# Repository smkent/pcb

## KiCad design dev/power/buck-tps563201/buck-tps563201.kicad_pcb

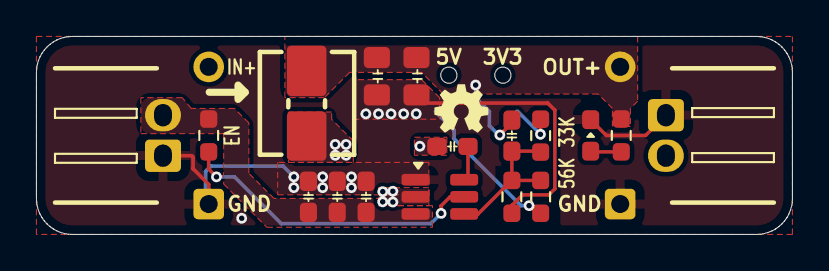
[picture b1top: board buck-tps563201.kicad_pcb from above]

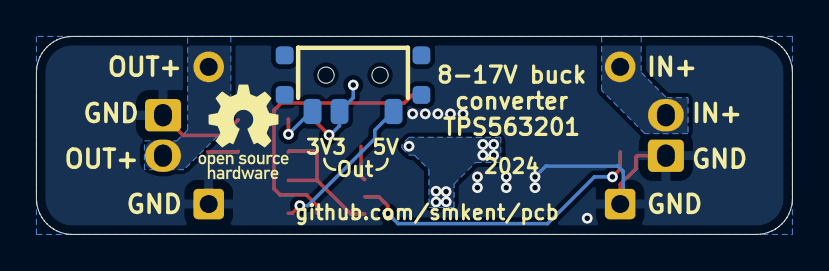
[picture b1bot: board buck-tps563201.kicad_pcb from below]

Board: 2 copper layers, 42.0 x 11.0 mm, 22 parts (5 on the bottom side), 10 nets.

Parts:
C1, C2: 10u; C_0603_1608Metric_Pad1.08x0.95mm_HandSolder
C3, C7: 0u1; C_0603_1608Metric_Pad1.08x0.95mm_HandSolder
C4: 75p; C_0603_1608Metric_Pad1.08x0.95mm_HandSolder
C8, C9: 22u; C_0805_2012Metric_Pad1.18x1.45mm_HandSolder
J1, J4: Conn_01x02; Conn_Combo_JST-1x02-XH_PH-THT-pad2gnd
J2, J5: Conn_01x03; PinHeader_1x01_P2.54mm_simple
J3, J6: Conn_01x03; PinHeader_1x01_P2.54mm_simple_square
L1: 4u7; Inductor_Multi_5.2x5.7_2x2.5
LED1: LED_Small; LED_0603_1608Metric_Pad1.05x0.95mm_HandSolder_simple
R0, R1, R4: 10K; R_0603_1608Metric_Pad0.98x0.95mm_HandSolder
R2: 56K; R_0603_1608Metric_Pad0.98x0.95mm_HandSolder
R3: 33K; R_0603_1608Metric_Pad0.98x0.95mm_HandSolder
SW1: SW_SPDT; SW-SMD_3P-P1.50_L2.7-W6.6
U1: TPS563200; SOT-23-6_Handsoldering_simple

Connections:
FB: C4.1, R1.2, R2.1, R3.2, U1.4 (VFB)
GND: C1.2, C2.2, C3.2, C8.2, C9.2, J1.2, J3.1, J4.2, J6.1, LED1.1 (K), R1.1, U1.1 (GND)
unnamed: LED1.2 (A), R0.1
unnamed: R2.2, SW1.1 (A)
unnamed: R3.1, SW1.3 (C)
unnamed: R4.2, U1.5 (EN)
unnamed: C7.1, U1.6 (VBST)
SW: C7.2, L1.1, U1.2 (SW)
VIN: C1.1, C2.1, C3.1, J1.1, J2.1, R4.1, U1.3 (VIN)
VOUT: C4.2, C8.1, C9.1, J4.1, J5.1, L1.2, R0.2, SW1.2 (B)

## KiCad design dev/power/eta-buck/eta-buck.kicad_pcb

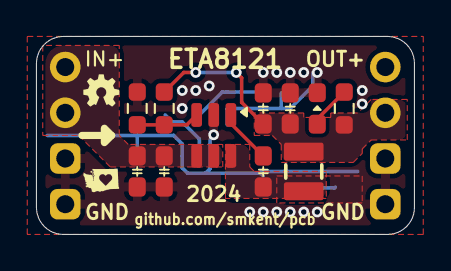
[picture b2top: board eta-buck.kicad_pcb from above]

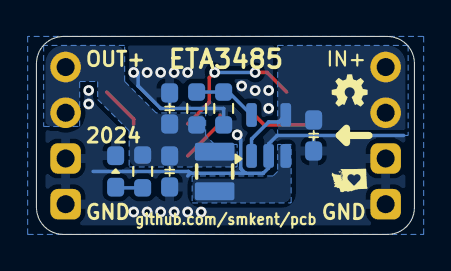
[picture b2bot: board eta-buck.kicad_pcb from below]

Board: 2 copper layers, 21.0 x 11.0 mm, 22 parts (11 on the bottom side), 10 nets.

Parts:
C0, C1, C4: 10u; C_0603_1608Metric_Pad1.08x0.95mm_HandSolder
C2, C3, C5, C6: 22u; C_0603_1608Metric_Pad1.08x0.95mm_HandSolder
C7: 10n; C_0603_1608Metric_Pad1.08x0.95mm_HandSolder
J1, J2: Pin headers; PinHeader_1x04_P2.54mm_Vertical_simple_pad3,4gnd
L1, L2: 4u7; IND-SMD_L2.5-W2.0_MHCHL2520
LED1, LED2: LED_Small; LED_0603_1608Metric_Pad1.05x0.95mm_HandSolder_simple
R1: 56K; R_0603_1608Metric_Pad0.98x0.95mm_HandSolder
R2, R3, R5, R6: 10K; R_0603_1608Metric_Pad0.98x0.95mm_HandSolder
R4: 75K; R_0603_1608Metric_Pad0.98x0.95mm_HandSolder
U1: ETA8121; SOT-23-6_simple
U2: ETA3485; SOT-23-5_simple

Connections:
/SW_B: L2.1, U2.3 (SW)
/SW_F: C7.2, L1.1, U1.6 (SW)
FB_B: R4.1, R5.2, U2.5 (FB)
FB_F: R1.1, R2.2, U1.3 (FB)
GND: C0.2, C1.2, C2.2, C3.2, C4.2, C5.2, C6.2, J1.3, J1.4, J2.3, J2.4, LED1.1 (K), LED2.1 (K), R2.1, R5.1, U1.2 (GND), U2.2 (GND)
unnamed: LED1.2 (A), R3.1
unnamed: LED2.2 (A), R6.1
unnamed: C7.1, U1.1 (BST)
VIN: C0.1, C1.1, C4.1, J1.1, J1.2, U1.4 (EN), U1.5 (VIN), U2.1 (EN), U2.4 (IN)
VOUT: C2.1, C3.1, C5.1, C6.1, J2.1, J2.2, L1.2, L2.2, R1.2, R3.2, R4.2, R6.2

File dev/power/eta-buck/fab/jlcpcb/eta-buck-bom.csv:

Comment,Designator,Footprint,LCSC
LED_Small,"LED1,LED2",custom:LED_0603_1608Metric_Pad1.05x0.95mm_HandSolder_simple,
10n,C7,custom:C_0603_1608Metric_Pad1.08x0.95mm_HandSolder,
56K,R1,Resistor_SMD:R_0603_1608Metric_Pad0.98x0.95mm_HandSolder,
ETA8121,U1,custom:SOT-23-6_simple,C7465509
75K,R4,Resistor_SMD:R_0603_1608Metric_Pad0.98x0.95mm_HandSolder,
10K,"R2,R3,R5,R6",Resistor_SMD:R_0603_1608Metric_Pad0.98x0.95mm_HandSolder,
22u,"C2,C3,C5,C6",custom:C_0603_1608Metric_Pad1.08x0.95mm_HandSolder,
10u,"C0,C1,C4",custom:C_0603_1608Metric_Pad1.08x0.95mm_HandSolder,
ETA3485,U2,custom:SOT-23-5_simple,C7465518
Pin headers,"J1,J2","custom:PinHeader_1x04_P2.54mm_Vertical_simple_pad3,4gnd",
4u7,"L1,L2",lcsc:IND-SMD_L2.5-W2.0_MHCHL2520,

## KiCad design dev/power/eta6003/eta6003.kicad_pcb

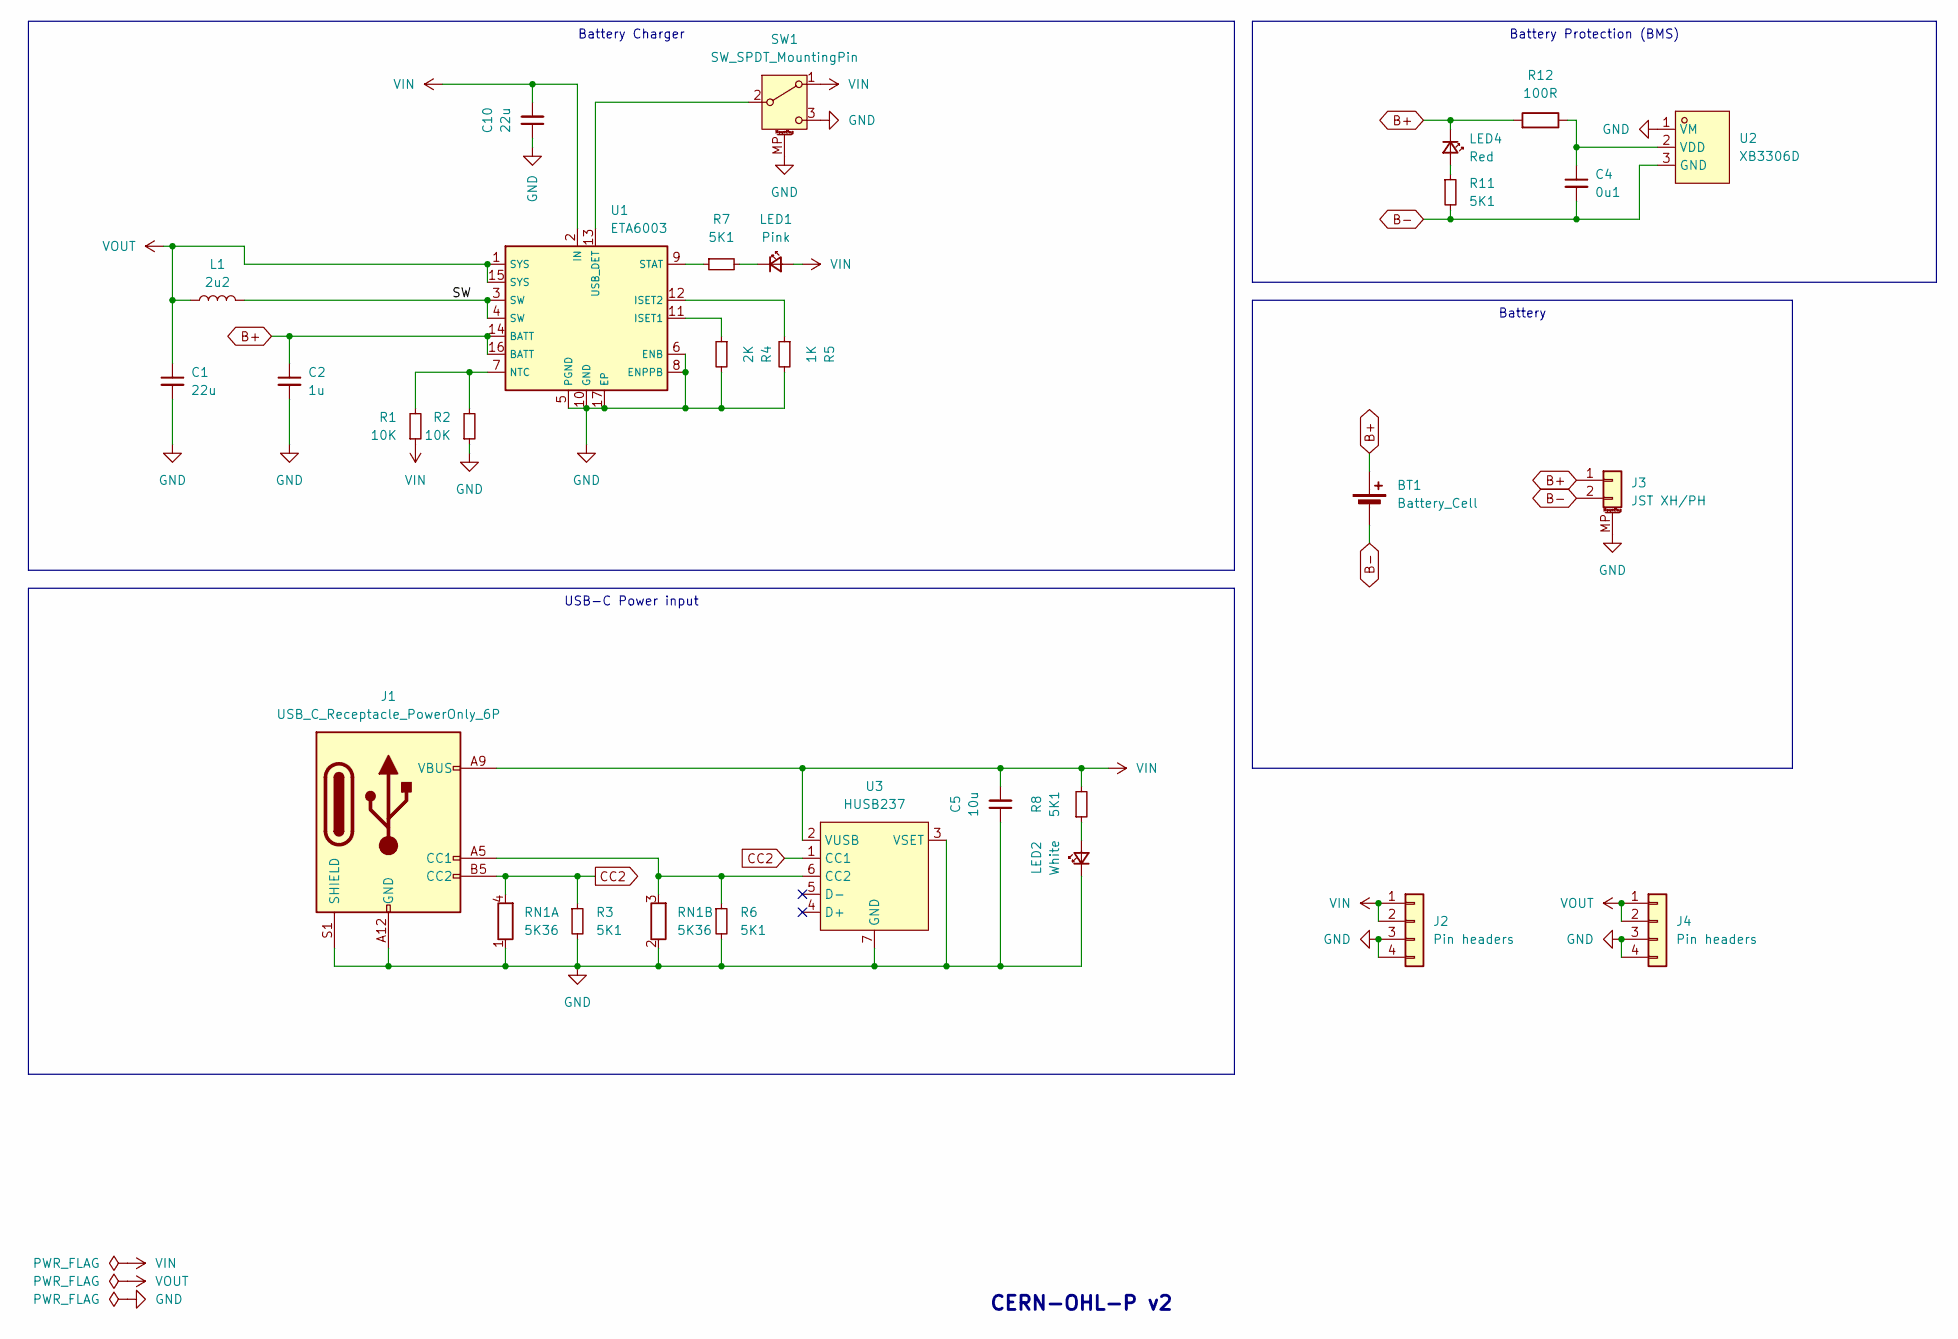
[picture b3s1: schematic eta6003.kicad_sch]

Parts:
BT1: Battery_Cell; BAT-TH_18650-A5BJ001
C1: 22u; C_0603_1608Metric_Pad1.08x0.95mm_HandSolder; LCSC Part C45783
C2: 1u; C_0603_1608Metric_Pad1.08x0.95mm_HandSolder; LCSC Part C52923
C4: 0u1; C_0603_1608Metric_Pad1.08x0.95mm_HandSolder; LCSC Part C1525
C5: 10u; C_0603_1608Metric_Pad1.08x0.95mm_HandSolder; LCSC Part C15850
C10: 22u; C_0805_2012Metric_Pad1.18x1.45mm_wide-center_HandSolder; LCSC Part C15850
J1: USB_C_Receptacle_PowerOnly_6P; USB_C_Receptacle_GCT_USB4125-xx-x_6P_TopMnt_Horizontal_hand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; LCSC Part C2927029
J2, J4: Pin headers; PinHeader_1x04_P2.54mm_Vertical_simple_pad3,4gnd
J3: JST XH/PH; Conn_Combo_JST-1x02-XH_PH-SMD-alt-pad2gnd
L1: 2u2; IND-SMD_L2.5-W2.0_MHCHL2520; LCSC Part C5832372
LED1: Pink; LED_0603_1608Metric_Pad1.05x0.95mm_HandSolder_simple
LED2: White; LED_0603_1608Metric_Pad1.05x0.95mm_HandSolder_simple
LED4: Red; LED_0603_1608Metric_Pad1.05x0.95mm_HandSolder_simple; LCSC Part C2286
R1, R2: 10K; R_0603_1608Metric_Pad0.98x0.95mm_HandSolder_simple; LCSC Part C25744
R3, R6, R11: 5K1; R_0603_1608Metric_Pad0.98x0.95mm_HandSolder_simple; LCSC Part C25905
R4: 2K; R_0603_1608Metric_Pad0.98x0.95mm_HandSolder; LCSC Part C22975
R5: 1K; R_0603_1608Metric_Pad0.98x0.95mm_HandSolder; LCSC Part C21190
R7, R8: 5K1; R_0603_1608Metric_Pad0.98x0.95mm_HandSolder_simple; LCSC Part C21190
R12: 100R; R_0603_1608Metric_Pad0.98x0.95mm_HandSolder_simple; LCSC Part C25076
RN1: 5K36; R_Array_Convex_2x0402
SW1: SW_SPDT_MountingPin; SW-SMD_3P-P1.50_L2.7-W6.6
U1: ETA6003; ETA6003_QFN-16-1EP_3x3mm_P0.5mm_EP1.7x1.7mm_ThermalVias; LCSC Part C5455585
U2: XB3306D; SOT-23_simple; LCSC Part C2759992
U3: HUSB237; DFN-6-1EP_2x2mm_P0.65mm_EP1x1.6mm; LCSC Part C7471904

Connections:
/SW: L1.2, U1.3 (SW), U1.4 (SW)
B+: BT1.1 (+), C2.1, J3.1, LED4.1 (K), R12.2, U1.14 (BATT), U1.16 (BATT)
B-: BT1.2 (-), C4.2, J3.2, R11.2, U2.3 (GND)
CC2: J1.B5 (CC2), R3.1, RN1.4 (R1.2), U3.1 (CC1)
GND: C1.2, C2.2, C5.1, C10.1, J1.A12 (GND), J1.B12 (GND), J1.S1 (SHIELD), J2.3, J2.4, J3.MP (MountPin), J4.3, J4.4, LED2.1 (K), R2.1, R3.2, R4.2, R5.2, R6.2, RN1.1 (R1.1), RN1.2 (R2.1), SW1.3 (C), SW1.MP (MountPin), U1.5 (PGND), U1.6 (ENB), U1.8 (ENPPB), U1.10 (GND), U1.17 (EP), U2.1 (VM), U3.3 (VSET), U3.7 (GND)
unnamed: J1.A5 (CC1), R6.1, RN1.3 (R2.2), U3.6 (CC2)
unnamed: LED1.1 (K), R7.2
unnamed: LED2.2 (A), R8.1
unnamed: LED4.2 (A), R11.1
unnamed: SW1.2 (B), U1.13 (USB_DET)
unnamed: R4.1, U1.11 (ISET1)
unnamed: R5.1, U1.12 (ISET2)
unnamed: R1.2, R2.2, U1.7 (NTC)
unnamed: R7.1, U1.9 (STAT)
unnamed: C4.1, R12.1, U2.2 (VDD)
VIN: C5.2, C10.2, J1.A9 (VBUS), J1.B9 (VBUS), J2.1, J2.2, LED1.2 (A), R1.1, R8.2, SW1.1 (A), U1.2 (IN), U3.2 (VUSB)
VOUT: C1.1, J4.1, J4.2, L1.1, U1.1 (SYS), U1.15 (SYS)

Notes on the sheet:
USB-C Power input
Battery Protection (BMS)
Battery Charger
Battery
CERN-OHL-P v2

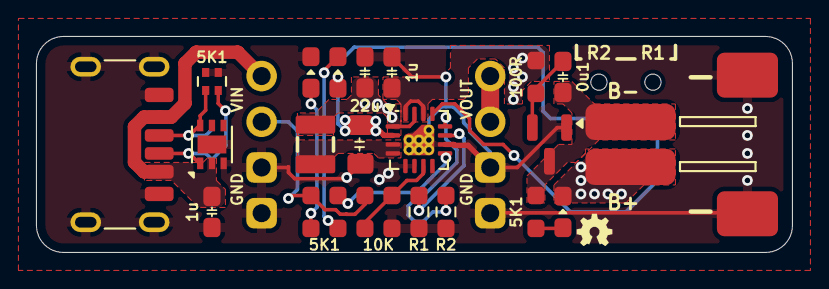
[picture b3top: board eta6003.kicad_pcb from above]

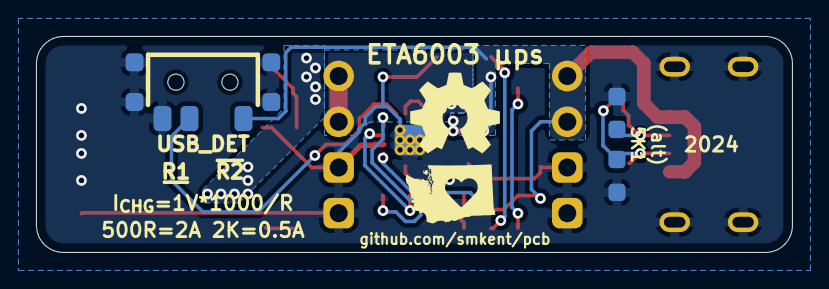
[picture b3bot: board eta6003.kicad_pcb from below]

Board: 2 copper layers, 42.0 x 12.0 mm, 28 parts (5 on the bottom side), 17 nets.

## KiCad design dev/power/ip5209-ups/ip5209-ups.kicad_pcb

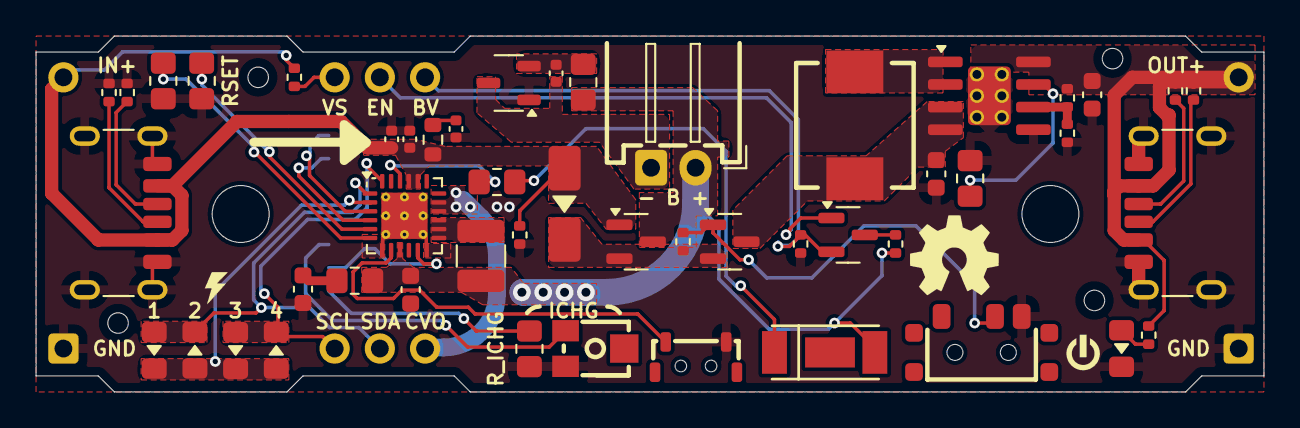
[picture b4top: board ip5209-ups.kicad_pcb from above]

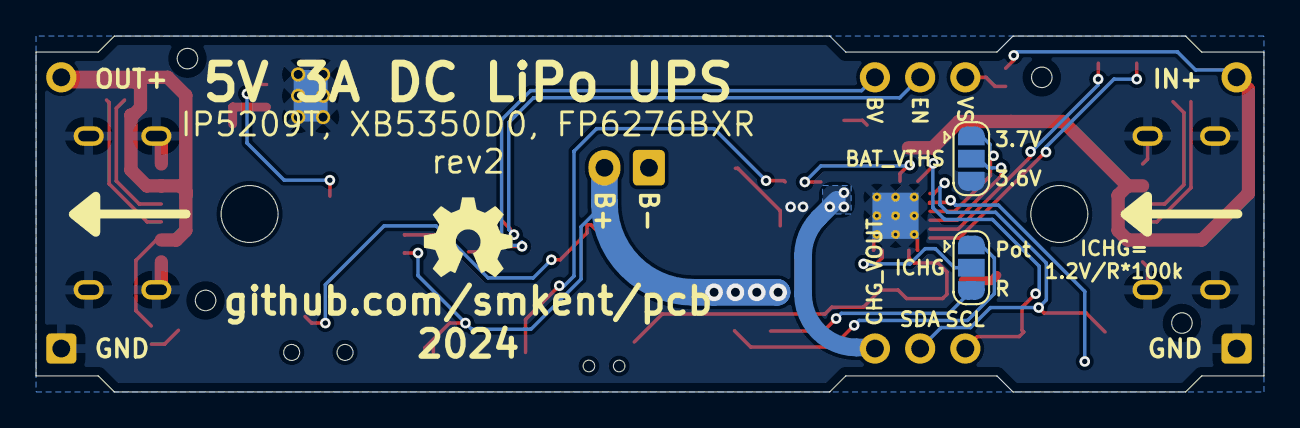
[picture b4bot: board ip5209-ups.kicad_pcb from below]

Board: 2 copper layers, 69.0 x 20.0 mm, 57 parts (8 on the bottom side), 38 nets.

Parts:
BT1: Battery_Cell; JST_XH_S2B-XH-2AW_1x02_P2.50mm_pad2gnd_trim
C1, C6: 10uF; C_0402_1005Metric
C2, C7, C10, C11: 22uF; C_0603_1608Metric
C3: 100nF; C_0402_1005Metric
C9: 0.1uF; C_0402_1005Metric
D1: SS34; D_SMA_simple
J1, J2: USB_C_Receptacle_PowerOnly_6P; USB_C_Receptacle_GCT_USB4125-xx-x_6P_TopMnt_Horizontal_hand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
J3, J9: Conn_01x03; PinHeader_1x03_P2.54mm_Vertical_simple
J5, J8: Conn_01x01; PinHeader_1x01_P2.54mm_simple
J11, J12: Conn_01x01; PinHeader_1x01_P2.54mm_simple_square
JP1, JP2: SolderJumper_3_Open; SolderJumper-3_P1.3mm_Open_RoundedPad1.0x1.5mm
L1: 1uH; L_1210_3225Metric
L2: 4.7uH; IND-SMD_L7.0-W6.6
LED1, LED2, LED3, LED4: LED_0805_2012Metric_Pad1.15x1.40mm_HandSolder_simple
LED5: LED-SMD_3P-L5.7-W3.0-RD
LED6: Boost; LED_0805_2012Metric_Pad1.15x1.40mm_HandSolder_simple
Q1, Q2: AO3401A; SOT-23
Q3: BSS138; SOT-23
R1: 120K; R_0805_2012Metric_Pad1.20x1.40mm_HandSolder
R2: 20R; R_0805_2012Metric_Pad1.20x1.40mm_HandSolder
R3: 2R; R_0603_1608Metric
R4: 0R5; R_0805_2012Metric_Pad1.20x1.40mm_HandSolder
R5: 100R; R_0805_2012Metric_Pad1.20x1.40mm_HandSolder
R6, R7, R9, R10, R13, R14, R15, R16, R17: 10K; R_0402_1005Metric
R8: 75K; R_0402_1005Metric
R11, R12: 5K1; R_0402_1005Metric
R18: 10K; R_0805_2012Metric_Pad1.20x1.40mm_HandSolder
R19: 47K; R_0805_2012Metric_Pad1.20x1.40mm_HandSolder
R20: 0R; R_0805_2012Metric_Pad1.20x1.40mm_HandSolder
RV1: R_Potentiometer_US; RES-ADJ-SMD_VG039NCH
SW1: SW_Push; SW-SMD_BZCN_TSA002A35XXX
SW2: SW_SPDT; SW-SMD_3P-P1.50_L2.7-W6.6
U1: IP5209T; QFN-24-1EP_4x4mm_P0.5mm_EP2.6x2.6mm_ThermalVias
U2: XB3306D; SOT-23-3
U3: FP6276BXR-G1; SOIC-8-1EP_3.9x4.9mm_P1.27mm_EP2.41x3.3mm_ThermalVias_Custo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

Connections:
B+: BT1.1 (+), C2.1, L1.2, LED5.2 (A), Q1.3 (D), R4.1, R5.1, R15.1, U1.9 (BAT)
B-: BT1.2 (-), C9.1, U2.3 (GND)
BATVDD: C9.2, R5.2, U2.2 (VDD)
BAT_SENSE: J9.1, Q3.2 (S), R16.1
BAT_SENSE_ENABLE: J9.2, Q3.1 (G)
BOOST: C10.1, L2.1, Q2.3 (D), U3.3 (VIN), U3.4 (EN)
BOOST_OC: R19.2, U3.7 (OC)
BOOST_SW: L2.2, U3.1 (LX), U3.2 (LX)
CHARGE_VOUT: J3.3, U1.16 (VOUT), U1.17 (VOUT)
FB: R8.2, R9.1, U3.6 (FB)
GND: C1.2, C2.2, C3.2, C6.2, C7.2, C10.2, C11.2, J1.A12 (GND), J1.B12 (GND), J1.S1 (SHIELD), J2.A12 (GND), J2.B12 (GND), J2.S1 (SHIELD), J11.1, J12.1, JP1.3 (B), LED6.1 (K), R1.2, R6.2, R9.2, R11.2, R12.2, R16.2, R18.2, R19.1, R20.1, RV1.3, SW1.1, SW2.3 (C), U1.7 (AGND), U1.12 (PGND), U1.25 (EP), U2.1 (VM), U3.5 (GND), U3.9 (EP)
ICHG: JP2.2 (C), U1.11 (ICHG)
KEY: SW1.2, U1.8 (KEY)
LED1: J3.1, LED3.2 (A), LED4.1 (K), U1.24 (L1)
LED2: J3.2, LED1.2 (A), LED2.1 (K), U1.1 (L2)
LED3: LED1.1 (K), LED2.2 (A), LED3.1 (K), LED4.2 (A), U1.2 (L3)
LIGHT: R2.1, U1.22 (LIGHT)
LOAD_SWITCH: D1.1 (K), Q1.2 (S), Q2.2 (S), R7.1
unnamed: C6.1, R3.2
unnamed: C7.1, R4.2
unnamed: J1.A5 (CC1), R12.1
unnamed: J1.B5 (CC2), R11.1
unnamed: J2.A5 (CC1), R13.2
unnamed: J2.B5 (CC2), R14.2
unnamed: JP2.1 (A), RV1.1
unnamed: JP2.3 (B), R1.1
unnamed: LED5.1 (K), R2.2
unnamed: LED6.2 (A), R10.2
unnamed: Q2.1 (G), R7.2, SW2.2 (B)
unnamed: Q3.3 (D), R15.2
unnamed: R20.2, U1.6 (NTC)
POWER_IN_SENSE: J9.3, R17.2
RSET: R18.1, U1.5 (RSET)
SW: L1.1, U1.13 (LX), U1.14 (LX), U1.15 (LX)
VIN: C1.1, C3.1, D1.2 (A), J1.A9 (VBUS), J1.B9 (VBUS), J5.1, Q1.1 (G), R3.1, R6.1, R17.1, U1.20 (VIN), U1.21 (VIN)
VOUT: C11.1, J2.A9 (VBUS), J2.B9 (VBUS), J8.1, R8.1, R10.1, R13.1, R14.1, U3.8 (VO)
VREG: JP1.1 (A), U1.3 (VREG)
VTHS: JP1.2 (C), U1.4 (VTHS)

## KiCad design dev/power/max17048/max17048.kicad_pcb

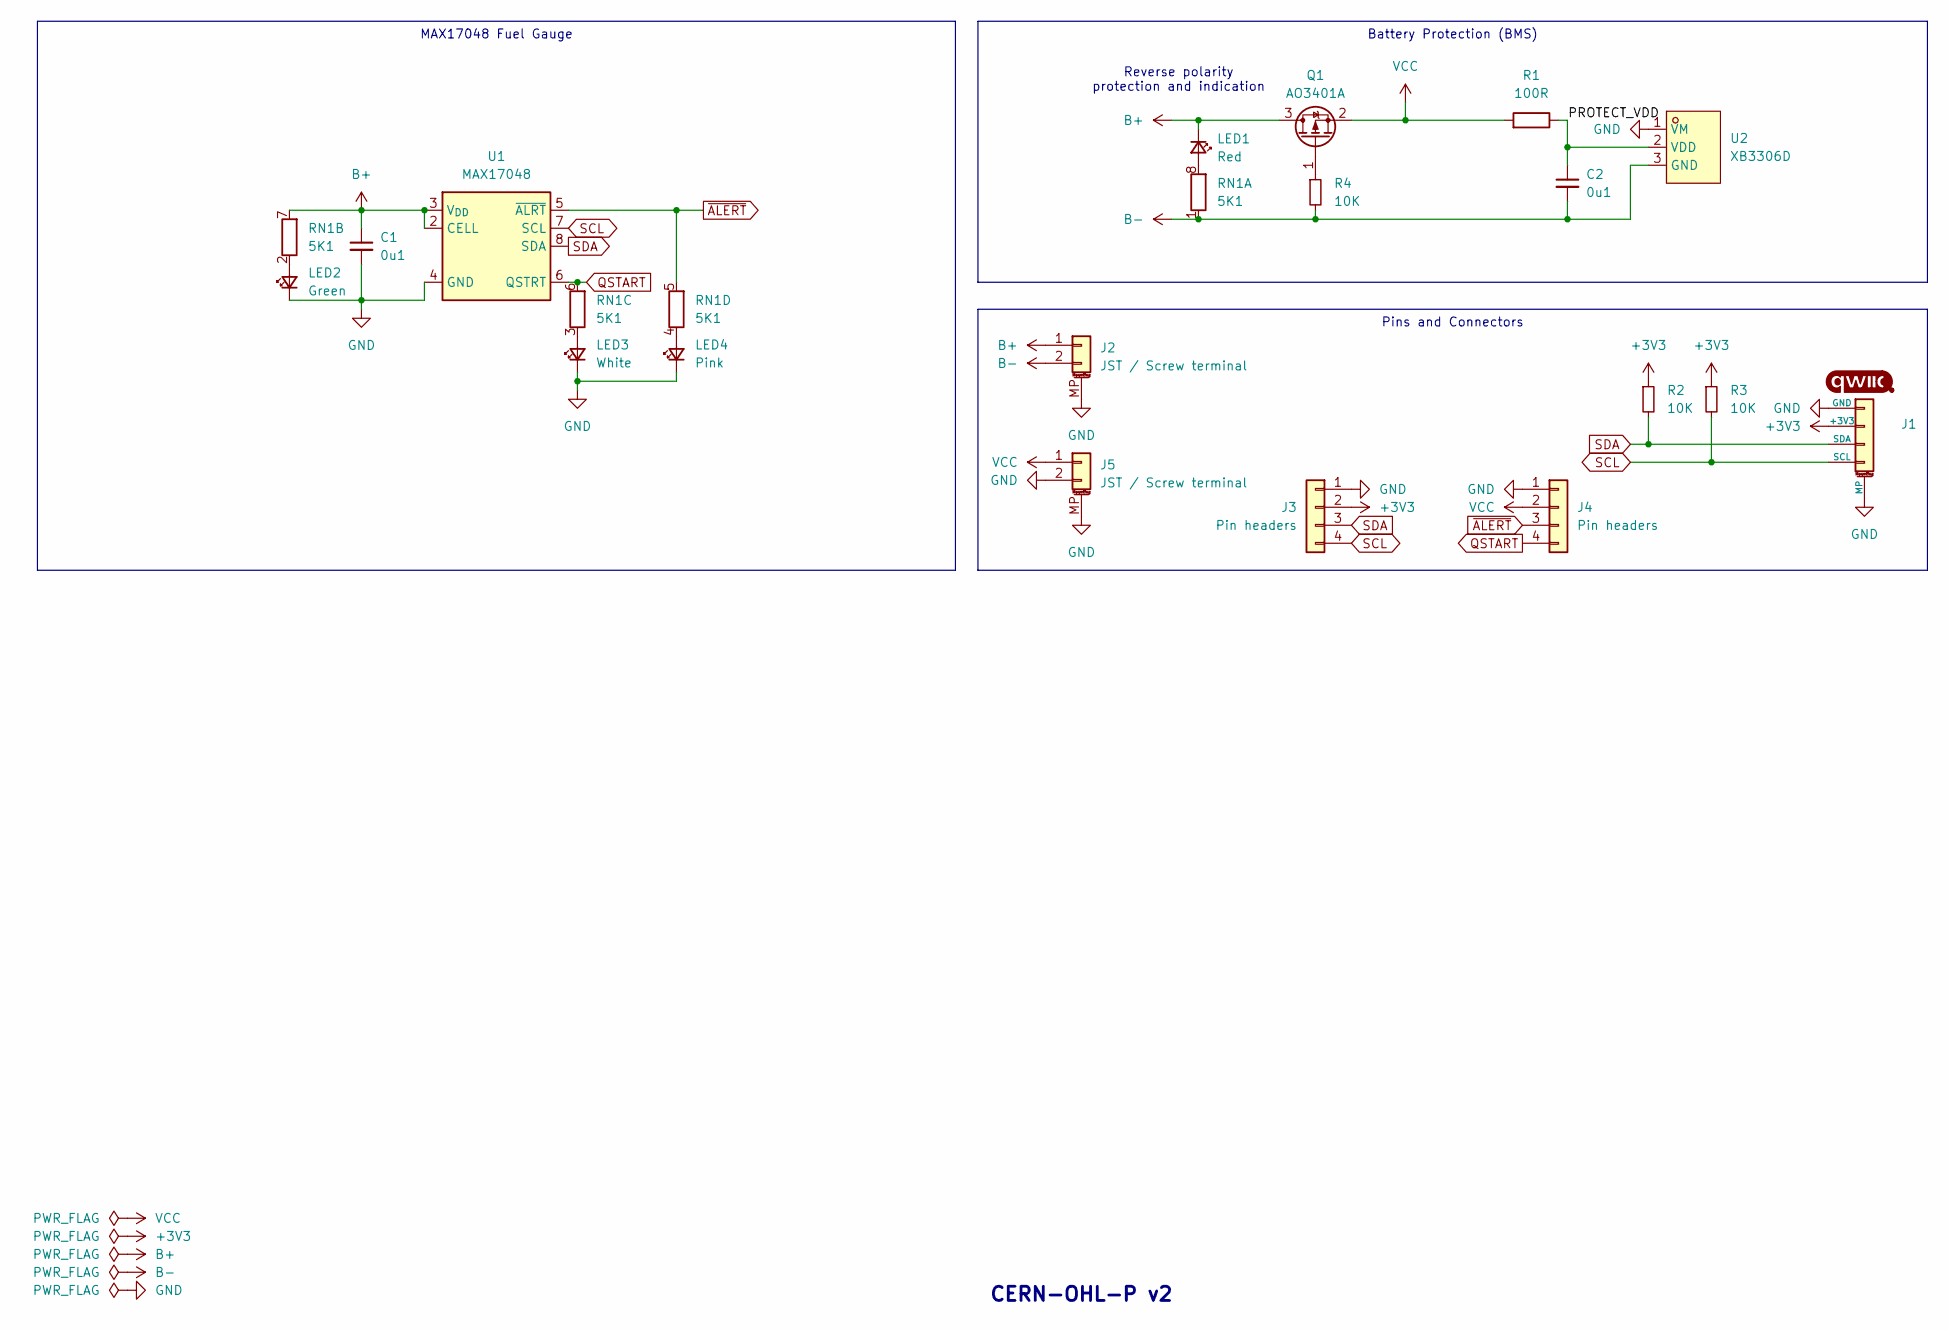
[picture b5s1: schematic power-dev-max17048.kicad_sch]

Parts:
C1, C2: 0u1; C_0603_1608Metric
J1: Qwiic; Qwiic-SMD-horizontal-logo-bottom-pinout
J2, J5: JST / Screw terminal; Conn_Combo_TerminalBlock_JST-1x02-XH_PH-pad2gnd
J3, J4: Pin headers; PinHeader_1x04_P2.54mm_Vertical_simple
LED1: Red; LED_0603_1608Metric_Pad1.05x0.95mm_HandSolder_simple; LCSC Part C2286
LED2: Green; LED_0603_1608Metric_Pad1.05x0.95mm_HandSolder_simple; LCSC Part C2286
LED3: White; LED_0603_1608Metric_Pad1.05x0.95mm_HandSolder_simple; LCSC Part C2286
LED4: Pink; LED_0603_1608Metric_Pad1.05x0.95mm_HandSolder_simple; LCSC Part C2286
Q1: AO3401A; SOT-23_simple
R1: 100R; R_0603_1608Metric_simple; LCSC Part C25076
R2, R3, R4: 10K; R_0603_1608Metric_simple
RN1: 5K1; R_Array_Convex_4x0603
U1: MAX17048; TDFN-8-1EP_2x2mm_P0.5mm_EP0.8x1.2mm; LCSC Part C2682616
U2: XB3306D; SOT-23_simple; LCSC Part C2759992

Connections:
+3V3: J1.2 (+3V3), J3.2, R2.1, R3.1
/PROTECT_VDD: C2.1, R1.1, U2.2 (VDD)
B+: C1.1, J2.1, LED1.1 (K), Q1.3 (D), RN1.7 (R2.2), U1.2 (CELL), U1.3 (V_{DD})
B-: C2.2, J2.2, R4.2, RN1.1 (R1.1), U2.3 (GND)
GND: C1.2, J1.1 (GND), J1.MP, J2.MP (MountPin), J3.1, J4.1, J5.2, J5.MP (MountPin), LED2.1 (K), LED3.1 (K), LED4.1 (K), U1.1 (CTG), U1.4 (GND), U1.9 (EP), U2.1 (VM)
unnamed: LED1.2 (A), RN1.8 (R1.2)
unnamed: LED2.2 (A), RN1.2 (R2.1)
unnamed: LED3.2 (A), RN1.3 (R3.1)
unnamed: LED4.2 (A), RN1.4 (R4.1)
unnamed: Q1.1 (G), R4.1
QSTART: J4.4, RN1.6 (R3.2), U1.6 (QSTRT)
SCL: J1.4 (SCL), J3.4, R3.2, U1.7 (SCL)
SDA: J1.3 (SDA), J3.3, R2.2, U1.8 (SDA)
VCC: J4.2, J5.1, Q1.2 (S), R1.2
~ALERT: J4.3, RN1.5 (R4.2), U1.5 (~ALRT)

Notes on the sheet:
MAX17048 Fuel Gauge
Pins and Connectors
Battery Protection (BMS)
CERN-OHL-P v2
Reverse polarity protection and indication

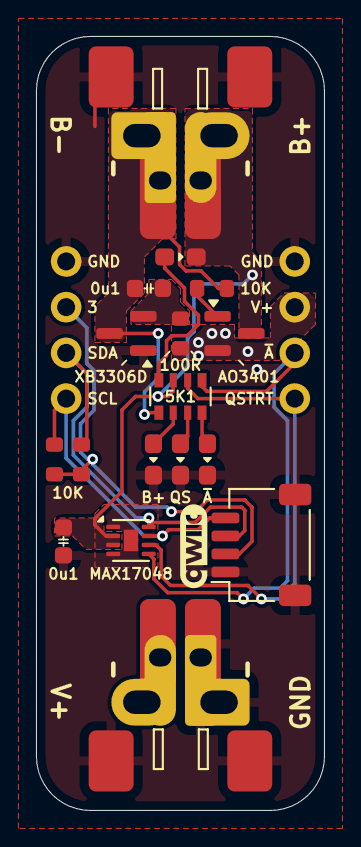
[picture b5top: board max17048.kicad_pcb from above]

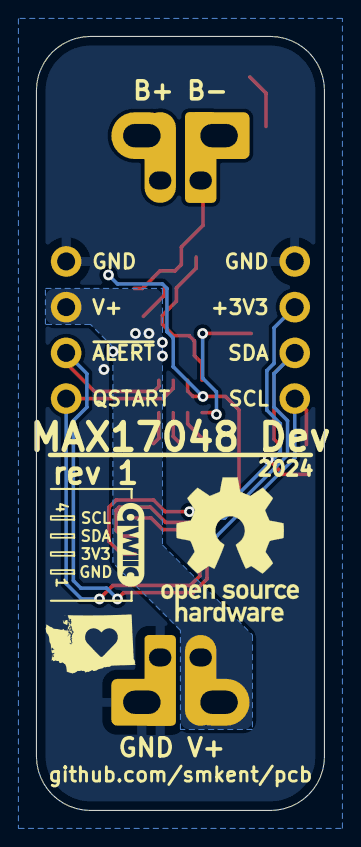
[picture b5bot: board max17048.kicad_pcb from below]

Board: 2 copper layers, 16.0 x 43.0 mm, 19 parts (2 on the bottom side), 15 nets.

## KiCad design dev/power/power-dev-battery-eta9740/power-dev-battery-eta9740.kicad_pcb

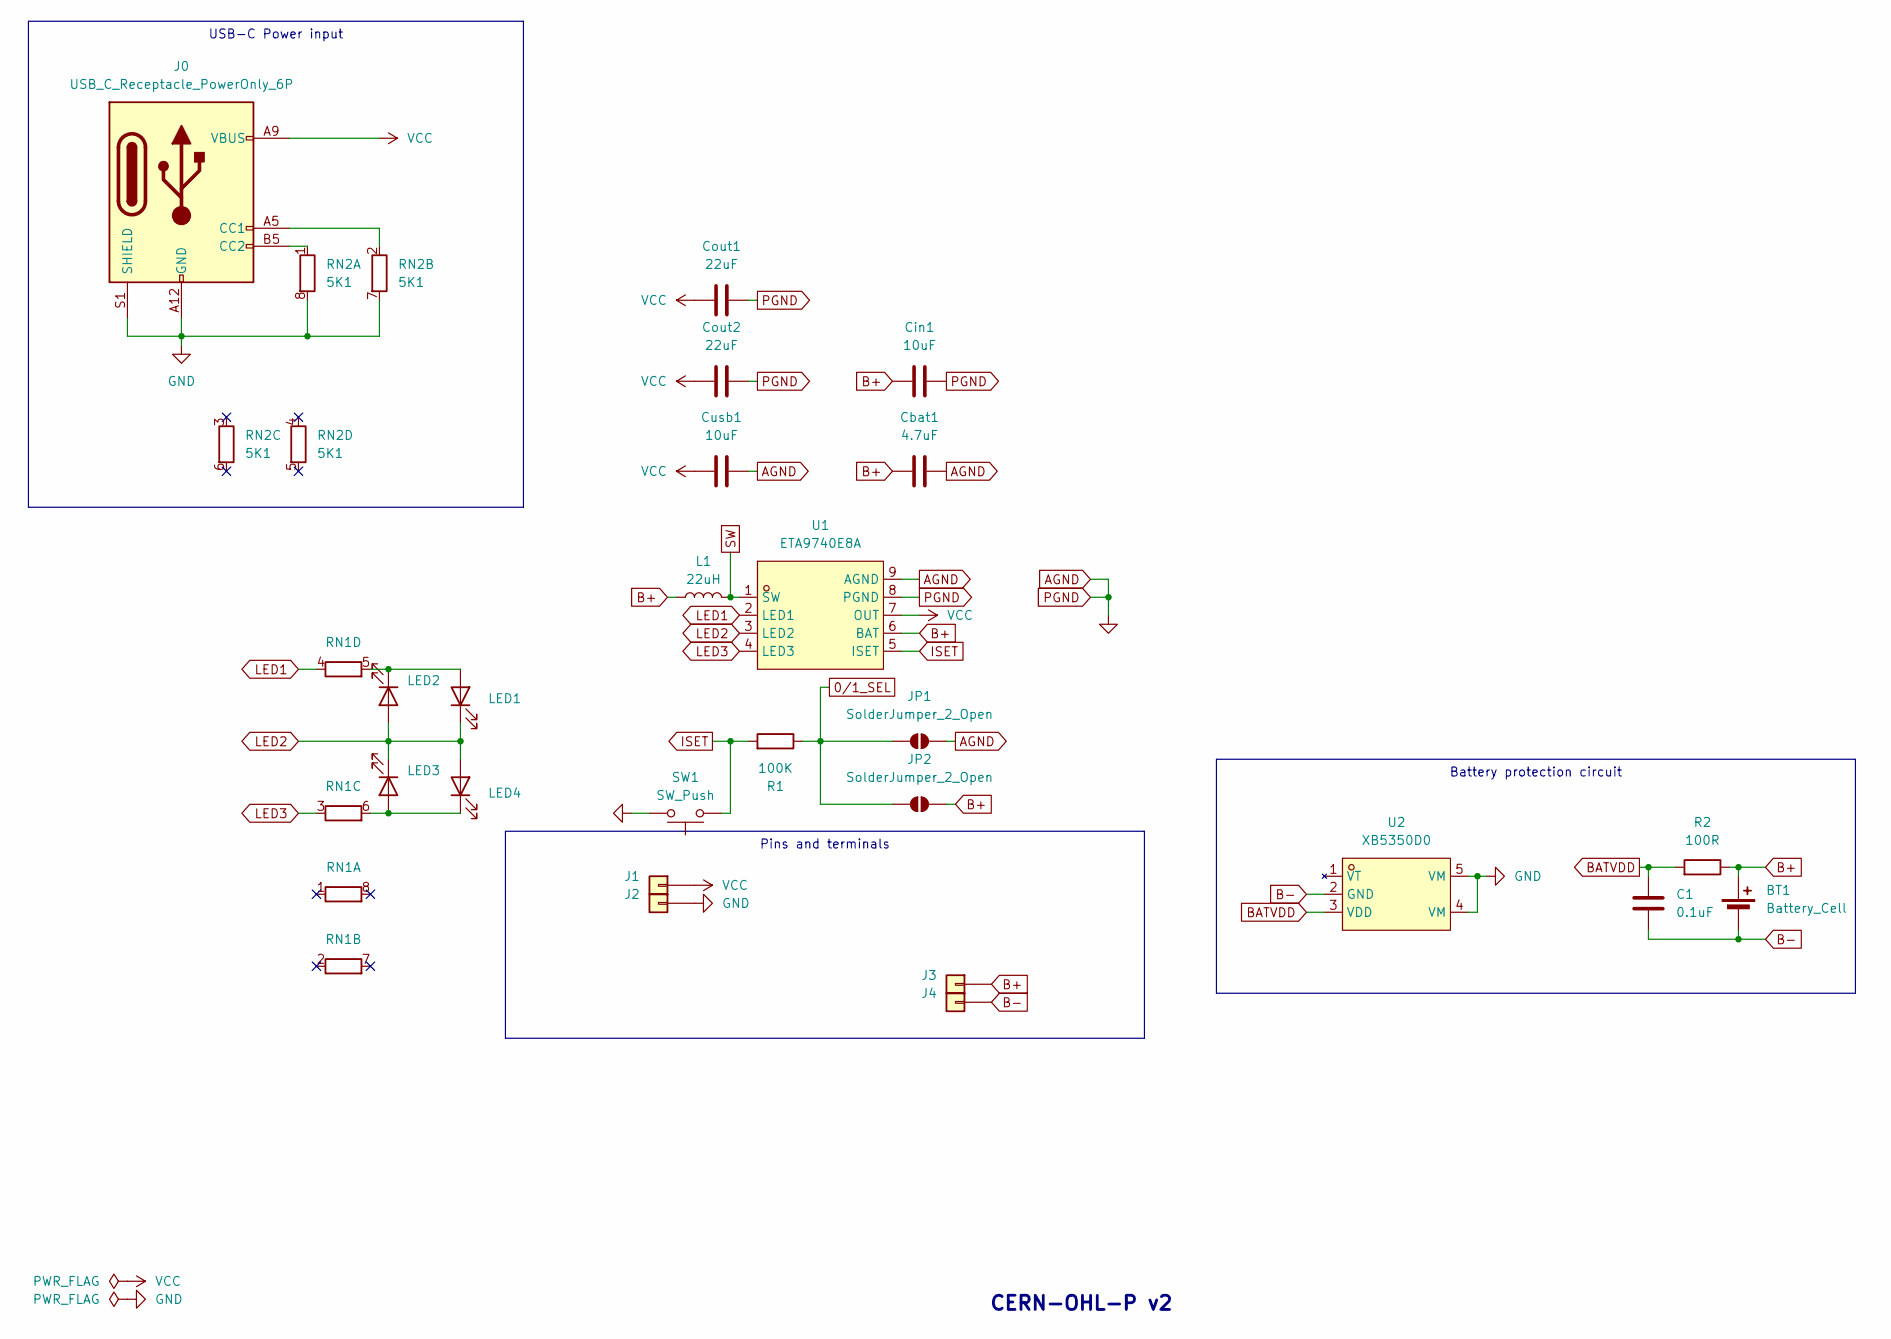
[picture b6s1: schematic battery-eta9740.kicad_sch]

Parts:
BT1: Battery_Cell; JST_XH_B2B-XH-A_1x02_P2.50mm_Vertical_simple_pad2gnd
C1: 0.1uF; C_0805_2012Metric_Pad1.18x1.45mm_HandSolder; LCSC Part C1525
Cbat1: 4.7uF; C_0805_2012Metric_Pad1.18x1.45mm_HandSolder
Cin1: 10uF; C_0805_2012Metric_Pad1.18x1.45mm_HandSolder
Cout1, Cout2: 22uF; C_0805_2012Metric_Pad1.18x1.45mm_HandSolder
Cusb1: 10uF; C_0805_2012Metric_Pad1.18x1.45mm_HandSolder
J0: USB_C_Receptacle_PowerOnly_6P; USB_C_Receptacle_GCT_USB4125-xx-x_6P_TopMnt_Horizontal_hand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
J1, J3: Conn_01x01; PinHeader_1x01_P2.54mm_simple
J2, J4: Conn_01x01; PinHeader_1x01_P2.54mm_simple_square
JP1, JP2: SolderJumper_2_Open; SolderJumper-2_P1.3mm_Open_RoundedPad1.0x1.5mm
L1: 22uH; Inductor_Multi_7.0x6.6_plus; LCSC Part C5832376
LED1, LED2, LED3, LED4: LED_0805_2012Metric_Pad1.15x1.40mm_HandSolder_simple
R1: 100K; R_0805_2012Metric_Pad1.20x1.40mm_HandSolder; LCSC Part C17379
R2: 100R; R_0805_2012Metric_Pad1.20x1.40mm_HandSolder
RN1: R_Pack04_Split; R_Array_Convex_4x0603
RN2: 5K1; R_Array_Convex_4x0603
SW1: SW_Push; PinHeader_1x02_P2.54mm_Vertical_simple_pad2gnd
U1: ETA9740E8A; SOIC-8-1EP_3.9x4.9mm_P1.27mm_EP2.41x3.3mm_ThermalVias_Custo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; LCSC Part C7465512
U2: XB5350D0; SOT-23-5_simple; JLCPCB_CORRECTION 0; 0; 180

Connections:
0/1_SEL: JP1.2 (B), JP2.1 (A), R1.1
AGND: Cbat1.1, Cin1.1, Cout1.2, Cout2.2, Cusb1.2, J0.A12 (GND), J0.B12 (GND), J0.S1 (SHIELD), J2.1, JP1.1 (A), RN2.7 (R2.2), RN2.8 (R1.2), SW1.2, U1.8 (PGND), U1.9 (AGND), U2.4 (VM), U2.5 (VM)
B+: BT1.1 (+), Cbat1.2, Cin1.2, J3.1, JP2.2 (B), L1.1, R2.1, U1.6 (BAT)
B-: BT1.2 (-), C1.1, J4.1, U2.2 (GND)
BATVDD: C1.2, R2.2, U2.3 (VDD)
ISET: R1.2, SW1.1, U1.5 (ISET)
LED1: RN1.4 (R4.1), U1.2 (LED1)
LED2: LED1.1 (K), LED2.2 (A), LED3.1 (K), LED4.2 (A), U1.3 (LED2)
LED3: RN1.3 (R3.1), U1.4 (LED3)
unnamed: J0.A5 (CC1), RN2.2 (R2.1)
unnamed: J0.B5 (CC2), RN2.1 (R1.1)
unnamed: LED1.2 (A), LED2.1 (K), RN1.5 (R4.2)
unnamed: LED3.2 (A), LED4.1 (K), RN1.6 (R3.2)
SW: L1.2, U1.1 (SW)
VCC: Cout1.1, Cout2.1, Cusb1.1, J0.A9 (VBUS), J0.B9 (VBUS), J1.1, U1.7 (OUT)

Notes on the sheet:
Pins and terminals
USB-C Power input
Battery protection circuit
CERN-OHL-P v2

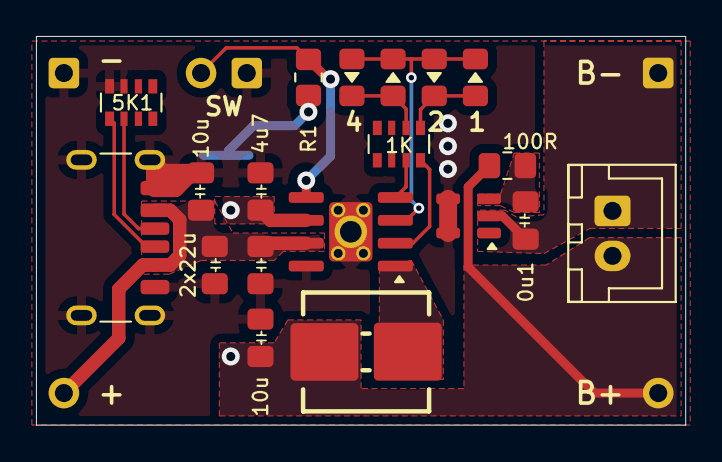
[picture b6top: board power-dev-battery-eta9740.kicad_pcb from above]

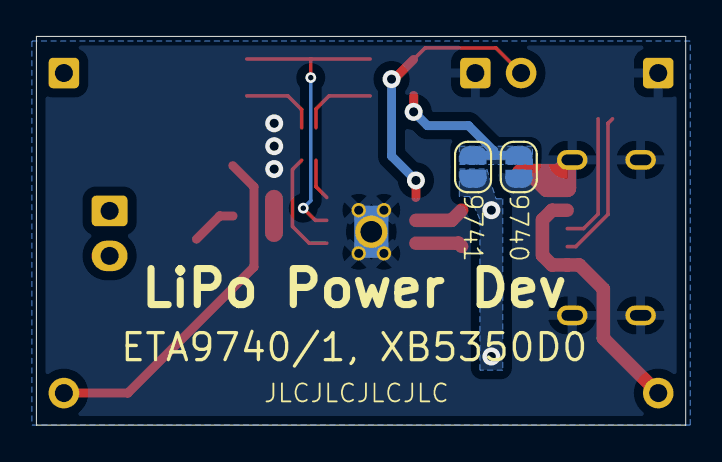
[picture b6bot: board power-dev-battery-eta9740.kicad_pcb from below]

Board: 2 copper layers, 36.1 x 21.6 mm, 26 parts (2 on the bottom side), 15 nets.

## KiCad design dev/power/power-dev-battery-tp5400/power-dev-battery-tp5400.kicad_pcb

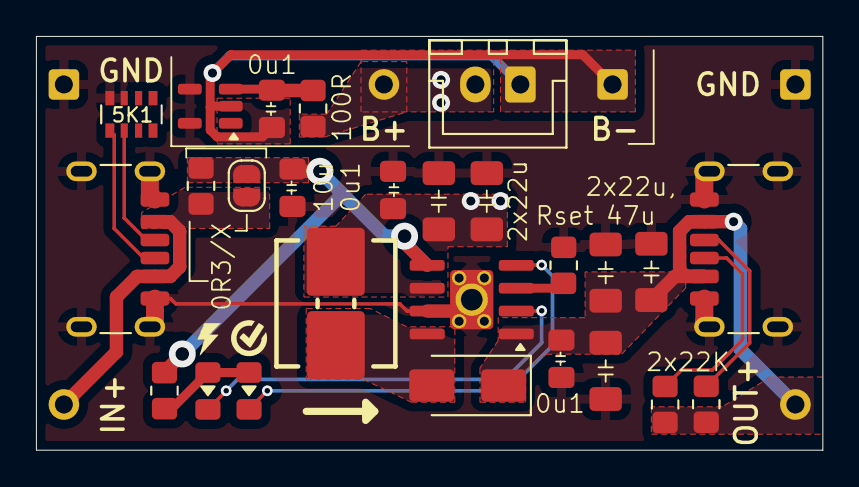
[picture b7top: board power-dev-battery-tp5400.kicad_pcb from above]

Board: 2 copper layers, 43.7 x 23.0 mm, 32 parts (0 on the bottom side), 16 nets.

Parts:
BT1: Battery_Cell; JST_XH_B2B-XH-A_1x02_P2.50mm_Vertical_simple_pad2gnd
C0: 0.1uF; C_0805_2012Metric_Pad1.18x1.45mm_HandSolder
C1: 10u; C_0805_2012Metric_Pad1.18x1.45mm_HandSolder
C2, C5: 0u1; C_0805_2012Metric_Pad1.18x1.45mm_HandSolder
C3, C4, C6, C7: 22u; C_1206_3216Metric_Pad1.33x1.80mm_HandSolder
C8: 47u; C_1206_3216Metric_Pad1.33x1.80mm_HandSolder
D3: SS34; D_SMA
J0, J7: USB_C_Receptacle_PowerOnly_6P; USB_C_Receptacle_GCT_USB4125-xx-x_6P_TopMnt_Horizontal_hand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
J1, J3, J5: Conn_01x01; PinHeader_1x01_P2.54mm_simple
J2, J4, J6: Conn_01x01; PinHeader_1x01_P2.54mm_simple_square
JP1: SolderJumper_2_Open; SolderJumper-2_P1.3mm_Open_RoundedPad1.0x1.5mm
L2: 10u; Inductor_Multi_7.0x6.6_plus
LED1, LED2: LED; LED_0805_2012Metric_Pad1.15x1.40mm_HandSolder_simple
R0: 0R3; R_0805_2012Metric_Pad1.20x1.40mm_HandSolder
R1: 1K; R_0805_2012Metric_Pad1.20x1.40mm_HandSolder
R2: 100R; R_0805_2012Metric_Pad1.20x1.40mm_HandSolder
R3: 1K1; R_0805_2012Metric_Pad1.20x1.40mm_HandSolder
R4, R5: 22K; R_0805_2012Metric_Pad1.20x1.40mm_HandSolder
RN1: 5K1; R_Array_Convex_4x0603
U1: TP5400_C2891434; SOIC-8-1EP_3.9x4.9mm_P1.27mm_EP2.41x3.3mm_ThermalVias_Custo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
U2: XB5350D0; SOT-23-5_simple

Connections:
B+: BT1.1 (+), C2.2, C3.2, C4.2, J3.1, L2.2, R2.1, U1.6 (BAT)
B-: BT1.2 (-), C0.1, J4.1, U2.2 (GND)
BATVDD: C0.2, R2.2, U2.3 (VDD)
GND: C1.1, C2.1, C3.1, C4.1, C5.1, C6.1, C7.1, C8.1, J0.A12 (GND), J0.B12 (GND), J0.S1 (SHIELD), J2.1, J6.1, J7.A12 (GND), J7.B12 (GND), J7.S1 (SHIELD), R3.1, RN1.7 (R2.2), RN1.8 (R1.2), U1.7 (GND), U1.9 (EP), U2.4 (VM), U2.5 (VM)
LED1: LED1.1 (K), U1.2 (~CHRG)
LED2: LED2.1 (K), U1.4 (~STDBY)
LX: D3.2 (A), L2.1, U1.8 (LX)
unnamed: J0.A5 (CC1), RN1.2 (R2.1)
unnamed: J0.B5 (CC2), RN1.1 (R1.1)
unnamed: J7.A5 (CC1), R4.2
unnamed: J7.B5 (CC2), R5.2
unnamed: LED1.2 (A), LED2.2 (A), R1.2
unnamed: R3.2, U1.3 (PROG)
VCC: J0.A9 (VBUS), J0.B9 (VBUS), J1.1, JP1.2 (B), R0.2
VIN: C1.2, JP1.1 (A), R0.1, R1.1, U1.5 (VCC)
VOUT: C5.2, C6.2, C7.2, C8.2, D3.1 (K), J5.1, J7.A9 (VBUS), J7.B9 (VBUS), R4.1, R5.1, U1.1 (VOUT)
